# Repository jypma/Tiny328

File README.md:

Tiny328
=======

This board is derived from the original Tiny328 project started by [Nathan Chantrell](http://nathan.chantrell.net/20130923/tiny328-mini-wireless-arduino-clone/). It has the following design goals:
- Software compatible with Arduino and JeeNode
- Includes an RFM12B radio module from HopeRF
- Easily mountable

Retaining the same form factor as the original Tiny328, I made the following changes:

- Redid the board in Kicad instead of Eagle
- Added two mounting holes
- Split up 3V3 and 5V power input headers
- Made the connection of RFM12B's DSSI pin to D4 optional by solder jumper
- Added footprints for an R1/R2 voltage divider from VCC into A0, so battery voltage
  can be reliably measured against a calibrated atmega 1.1V band gap reference.

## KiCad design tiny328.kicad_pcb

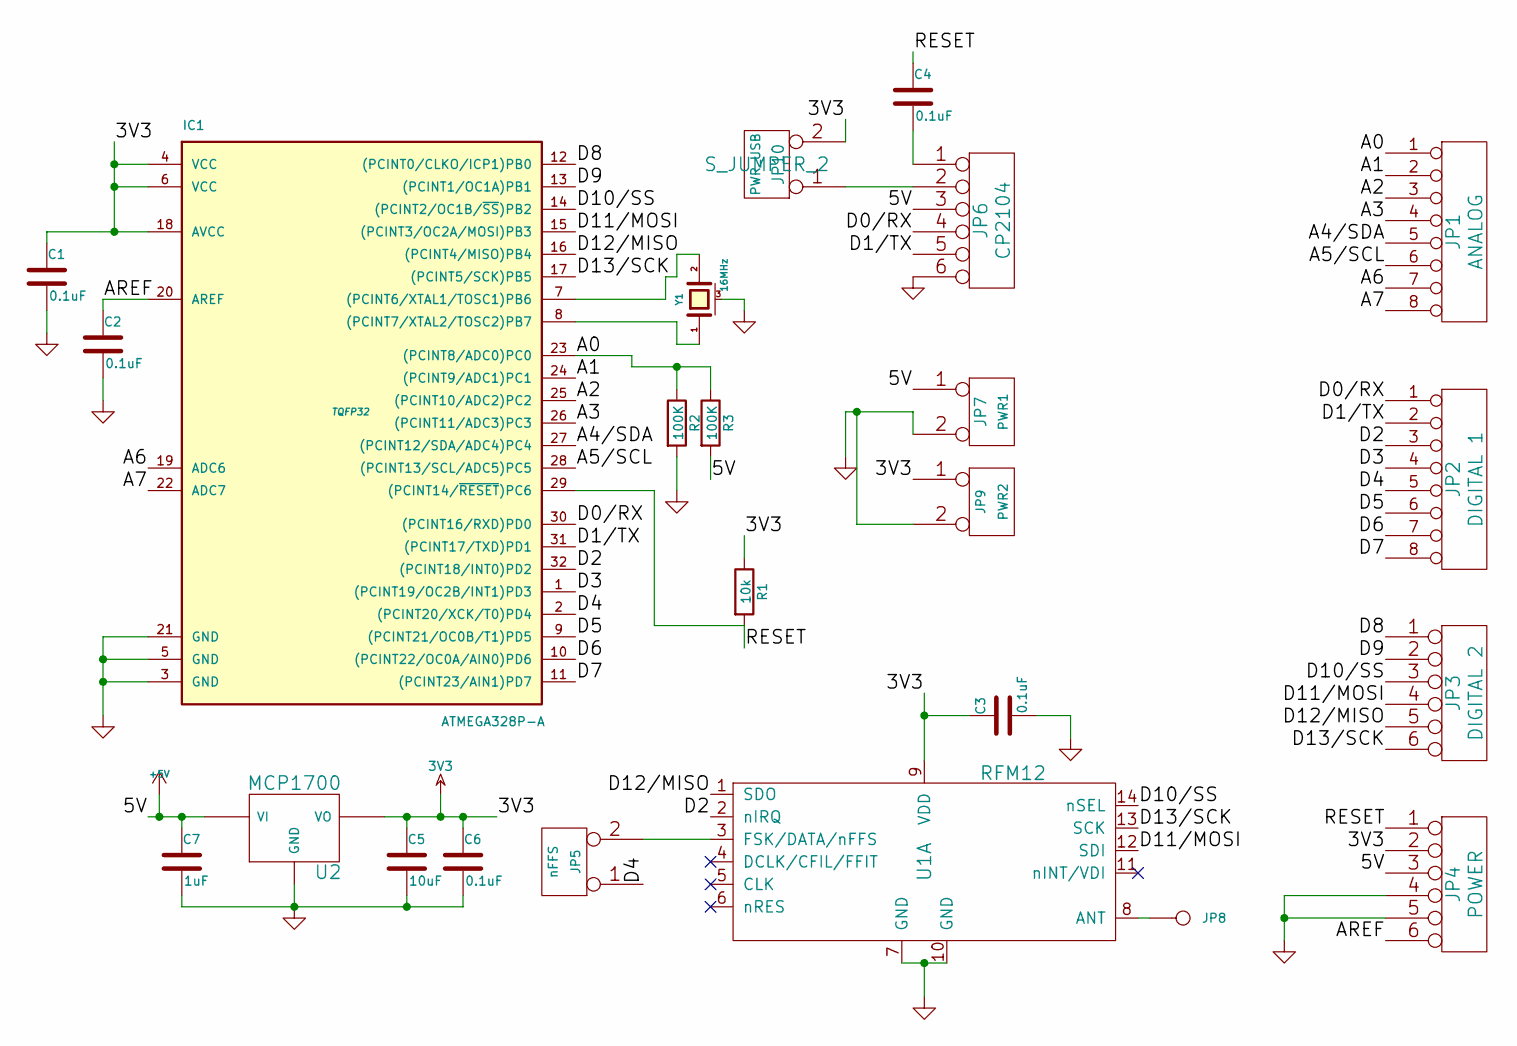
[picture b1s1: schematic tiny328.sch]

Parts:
C1, C2, C3, C4, C6: 0.1uF
C5: 10uF
C7: 1uF
IC1: ATMEGA328P-A; TQFP32
JP1: ANALOG
JP2: DIGITAL 1
JP3: DIGITAL 2
JP4: POWER
JP5: nFFS
JP6: CP2104
JP7: PWR1
JP8: ANT
JP9: PWR2
JP10: PWR_USB; S_JUMPER_2
R1: 10k
R2, R3: 100K
U1: RFM12
U2: MCP1700
Y1: 16MHz

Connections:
3V3: C1.1, C3.1, C5.1, C6.1, IC1.4 (VCC), IC1.6 (VCC), IC1.18 (AVCC), JP4.2, JP9.1, JP10.2 (PM), R1.1, U1.9 (VDD), U2.2 (VO)
+5V: C7.1, JP4.3, JP6.3, JP7.1, R3.2, U2.3 (VI)
/A0: IC1.23 ((PCINT8/ADC0)PC0), JP1.1, R2.1, R3.1
/A1: IC1.24 ((PCINT9/ADC1)PC1), JP1.2
/A2: IC1.25 ((PCINT10/ADC2)PC2), JP1.3
/A3: IC1.26 ((PCINT11/ADC3)PC3), JP1.4
/A4/SDA: IC1.27 ((PCINT12/SDA/ADC4)PC4), JP1.5
/A5/SCL: IC1.28 ((PCINT13/SCL/ADC5)PC5), JP1.6
/A6: IC1.19 (ADC6), JP1.7
/A7: IC1.22 (ADC7), JP1.8
/AREF: C2.1, IC1.20 (AREF), JP4.6
/D0/RX: IC1.30 ((PCINT16/RXD)PD0), JP2.1, JP6.4
/D1/TX: IC1.31 ((PCINT17/TXD)PD1), JP2.2, JP6.5
/D2: IC1.32 ((PCINT18/INT0)PD2), JP2.3, U1.2 (nIRQ)
/D3: IC1.1 ((PCINT19/OC2B/INT1)PD3), JP2.4
/D4: IC1.2 ((PCINT20/XCK/T0)PD4), JP2.5, JP5.1
/D5: IC1.9 ((PCINT21/OC0B/T1)PD5), JP2.6
/D6: IC1.10 ((PCINT22/OC0A/AIN0)PD6), JP2.7
/D7: IC1.11 ((PCINT23/AIN1)PD7), JP2.8
/D8: IC1.12 ((PCINT0/CLKO/ICP1)PB0), JP3.1
/D9: IC1.13 ((PCINT1/OC1A)PB1), JP3.2
/D10/SS: IC1.14 ((PCINT2/OC1B/~SS~)PB2), JP3.3, U1.14 (nSEL)
/D11/MOSI: IC1.15 ((PCINT3/OC2A/MOSI)PB3), JP3.4, U1.12 (SDI)
/D12/MISO: IC1.16 ((PCINT4/MISO)PB4), JP3.5, U1.1 (SDO)
/D13/SCK: IC1.17 ((PCINT5/SCK)PB5), JP3.6, U1.13 (SCK)
/RESET: C4.1, IC1.29 ((PCINT14/~RESET~)PC6), JP4.1, R1.2
GND: C1.2, C2.2, C3.2, C5.2, C6.2, C7.2, IC1.3 (GND), IC1.5 (GND), IC1.21 (GND), JP4.4, JP4.5, JP6.6, JP7.2 (PM), JP9.2 (PM), R2.2, U1.7 (GND), U1.10 (GND), U2.1 (GND), Y1.3 (case)
unnamed: C4.2, JP6.1
unnamed: IC1.7 ((PCINT6/XTAL1/TOSC1)PB6), Y1.2
unnamed: IC1.8 ((PCINT7/XTAL2/TOSC2)PB7), Y1.1
unnamed: JP5.2 (PM), U1.3 (FSK/DATA/nFFS)
unnamed: JP8.1, U1.8 (ANT)
unnamed: JP6.2, JP10.1

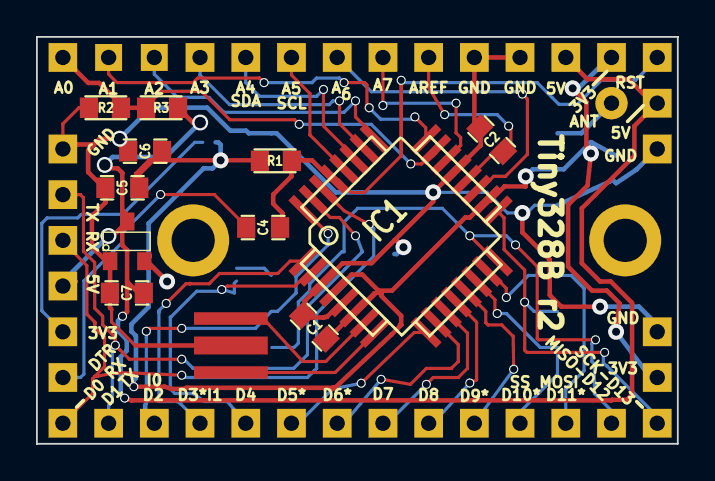
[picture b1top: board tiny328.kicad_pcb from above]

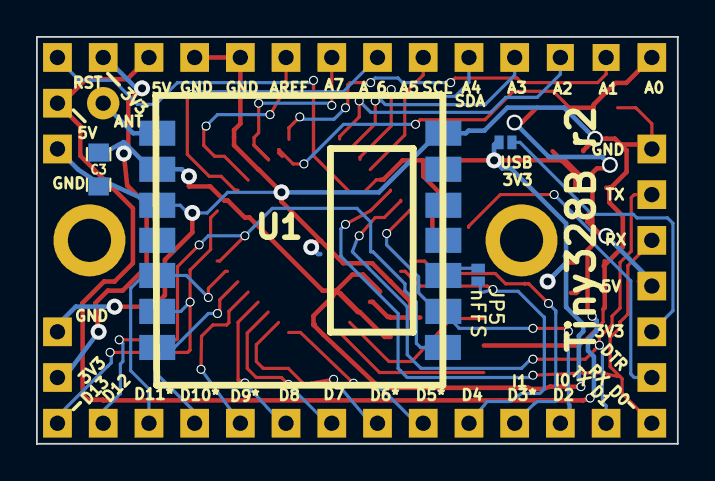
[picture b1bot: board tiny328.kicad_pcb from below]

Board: 2 copper layers, 35.6 x 22.6 mm, 26 parts (4 on the bottom side), 33 nets.

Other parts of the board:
1PIN, 1PIN#2: P***; 1pin_only

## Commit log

2014-10-02 initial version
2014-10-05 more routing, mounting holes
2014-10-06 routing complete
2014-10-06 increase power track widths
2014-10-12 widen vias
2014-10-27 all connected, flooded
2014-11-02 first version sent to osh park
2014-11-05 add board png
2014-11-05 add readme
2014-12-10 Increase header hole & pad size Fix MCP1800 reversed pins 2 & 3 Fix FTDI reversed TX & RX Add MISO & SCK labels Remove silk screen around mounting holes Increase pad size for 0603's for hand soldering
2014-12-10 don't version bak files
2014-12-10 update layout pic and add schematic pdf
2014-12-12 adjust silk screen to be visible when headers are mounted
2015-02-13 increase antenna trace width
2015-04-23 small tweaks
2015-05-11 change to CP2104
